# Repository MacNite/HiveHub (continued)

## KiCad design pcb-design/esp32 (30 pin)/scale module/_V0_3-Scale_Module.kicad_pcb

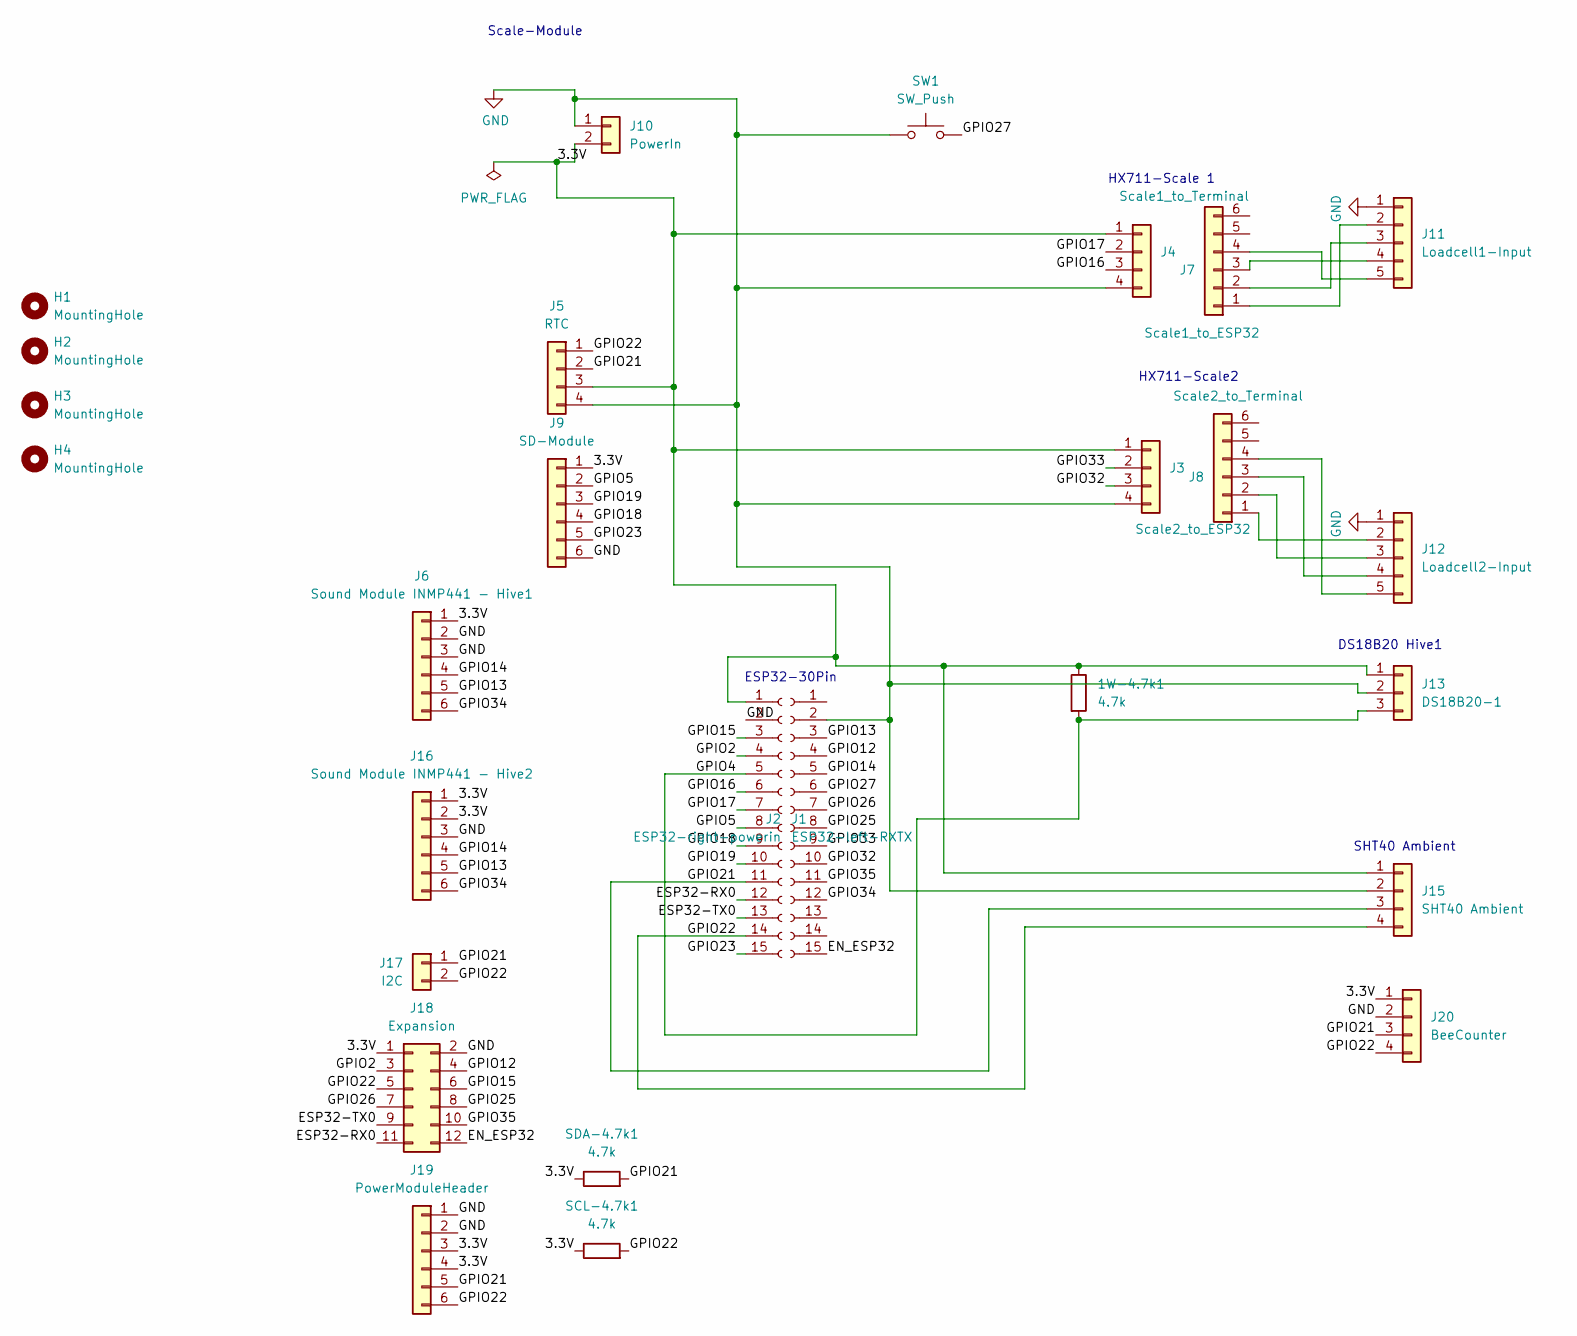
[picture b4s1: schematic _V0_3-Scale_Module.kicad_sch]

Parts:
1W-4.7k1: 4.7k; R_Axial_DIN0207_L6.3mm_D2.5mm_P7.62mm_Horizontal
H1, H2, H3, H4: MountingHole; MountingHole_3.2mm_M3
J1: ESP32-left-RXTX; PinSocket_1x15_P2.54mm_Vertical
J2: ESP32-right-powerin; PinHeader_1x15_P2.54mm_Vertical
J3: Scale2_to_ESP32; PinSocket_1x04_P2.54mm_Vertical
J4: Scale1_to_ESP32; PinSocket_1x04_P2.54mm_Vertical
J5: RTC; PinSocket_1x04_P2.54mm_Vertical
J6: Sound Module INMP441 - Hive1; JST_XH_B6B-XH-A_1x06_P2.50mm_Vertical
J7: Scale1_to_Terminal; PinSocket_1x06_P2.54mm_Vertical
J8: Scale2_to_Terminal; PinSocket_1x06_P2.54mm_Vertical
J9: SD-Module; PinSocket_1x06_P2.54mm_Vertical
J10: PowerIn; TerminalBlock_Xinya_XY308-2.54-2P_1x02_P2.54mm_Horizontal
J11: Loadcell1-Input; JST_XH_B5B-XH-A_1x05_P2.50mm_Vertical
J12: Loadcell2-Input; JST_XH_B5B-XH-A_1x05_P2.50mm_Vertical
J13: DS18B20-1; JST_XH_B3B-XH-A_1x03_P2.50mm_Vertical
J15: SHT40 Ambient; JST_XH_B4B-XH-A_1x04_P2.50mm_Vertical
J16: Sound Module INMP441 - Hive2; JST_XH_B6B-XH-A_1x06_P2.50mm_Vertical
J17: I2C; TerminalBlock_Xinya_XY308-2.54-2P_1x02_P2.54mm_Horizontal
J18: Expansion; PinHeader_2x06_P2.54mm_Vertical
J19: PowerModuleHeader; PinHeader_1x06_P2.54mm_Vertical
J20: BeeCounter; JST_XH_B4B-XH-A_1x04_P2.50mm_Vertical
SCL-4.7k1: 4.7k; R_Axial_DIN0207_L6.3mm_D2.5mm_P7.62mm_Horizontal
SDA-4.7k1: 4.7k; R_Axial_DIN0207_L6.3mm_D2.5mm_P7.62mm_Horizontal
SW1: SW_Push; PinSocket_1x02_P2.54mm_Vertical

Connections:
/3.3V: 1W-4.7k1.1, J1.1, J3.1, J4.1, J5.3, J6.1, J9.1, J10.2, J13.1, J15.1, J16.1, J16.2, J18.1, J19.3, J19.4, J20.1, SCL-4.7k1.1, SDA-4.7k1.1
/EN_ESP32: J2.15, J18.12
/ESP32-RX0: J1.12, J18.11
/ESP32-TX0: J1.13, J18.9
/GPIO2: J1.4, J18.3
/GPIO4: 1W-4.7k1.2, J1.5, J13.3
/GPIO5: J1.8, J9.2
/GPIO12: J2.4, J18.4
/GPIO13: J2.3, J6.5, J16.5
/GPIO14: J2.5, J6.4, J16.4
/GPIO15: J1.3, J18.6
/GPIO16: J1.6, J4.3
/GPIO17: J1.7, J4.2
/GPIO18: J1.9, J9.4
/GPIO19: J1.10, J9.3
/GPIO21: J1.11, J5.2, J15.3, J17.1, J19.5, J20.3, SDA-4.7k1.2
/GPIO22: J1.14, J5.1, J15.4, J17.2, J18.5, J19.6, J20.4, SCL-4.7k1.2
/GPIO23: J1.15, J9.5
/GPIO25: J2.8, J18.8
/GPIO26: J2.7, J18.7
/GPIO27: J2.6, SW1.2
/GPIO32: J2.10, J3.3
/GPIO33: J2.9, J3.2
/GPIO34: J2.12, J6.6, J16.6
/GPIO35: J2.11, J18.10
GND: J1.2, J2.2, J3.4, J4.4, J5.4, J6.2, J6.3, J9.6, J10.1, J11.1, J12.1, J13.2, J15.2, J16.3, J18.2, J19.1, J19.2, J20.2, SW1.1
unnamed: J7.1, J11.2
unnamed: J7.2, J11.3
unnamed: J7.3, J11.4
unnamed: J7.4, J11.5
unnamed: J8.1, J12.2
unnamed: J8.2, J12.3
unnamed: J8.3, J12.4
unnamed: J8.4, J12.5

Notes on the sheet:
Scale-Module
HX711-Scale2
DS18B20 Hive1
SHT40 Ambient
ESP32-30Pin
HX711-Scale 1

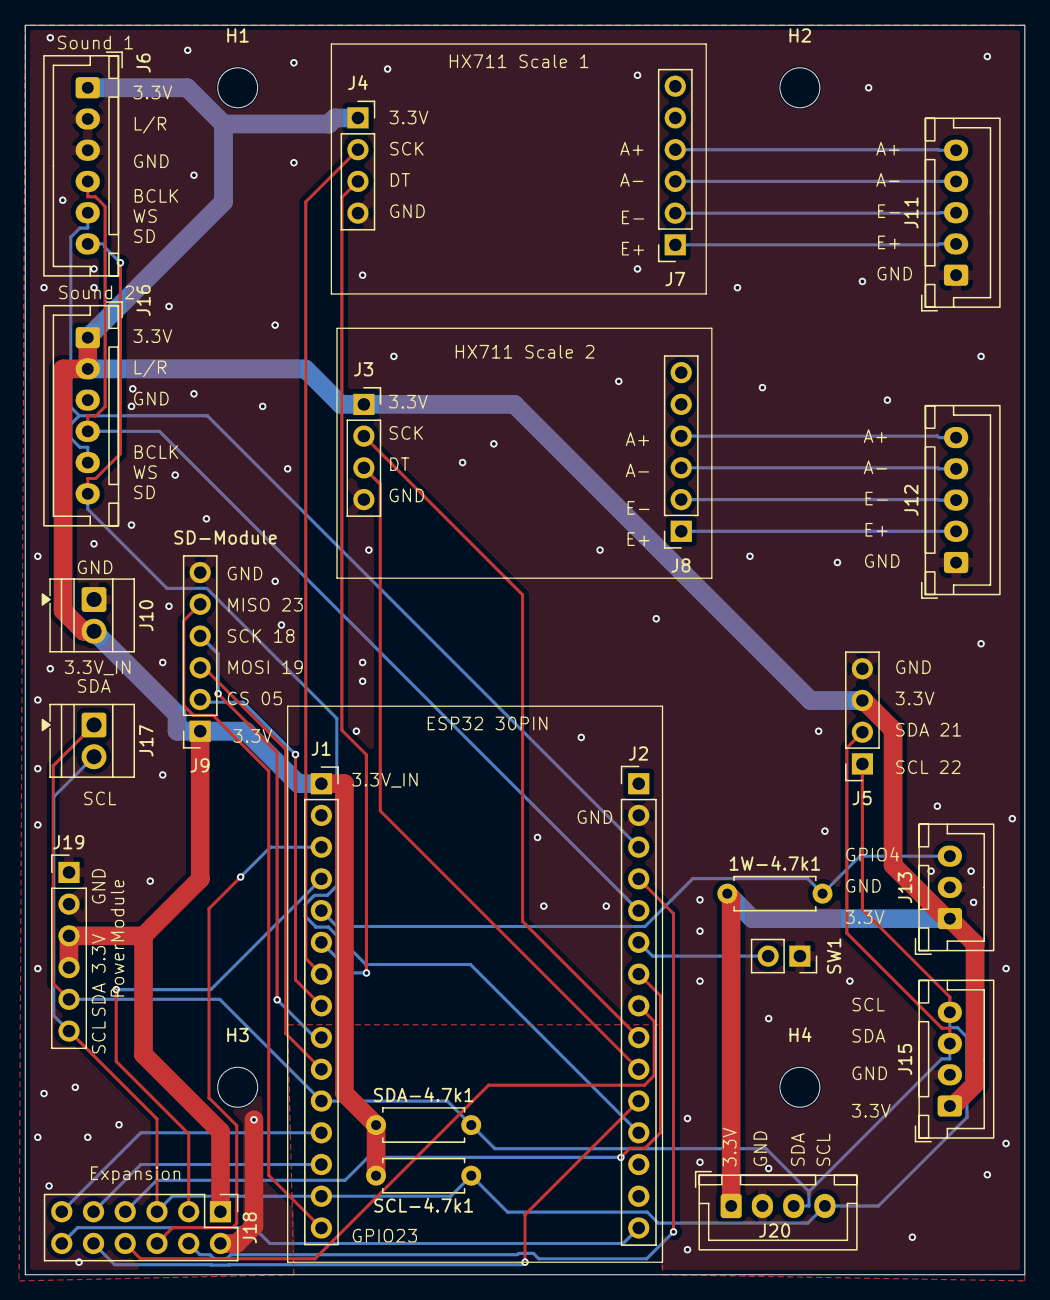
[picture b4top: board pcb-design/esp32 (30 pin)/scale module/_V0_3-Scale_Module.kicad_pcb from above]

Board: 2 copper layers, 80.0 x 100.0 mm, 27 parts (0 on the bottom side), 34 nets.

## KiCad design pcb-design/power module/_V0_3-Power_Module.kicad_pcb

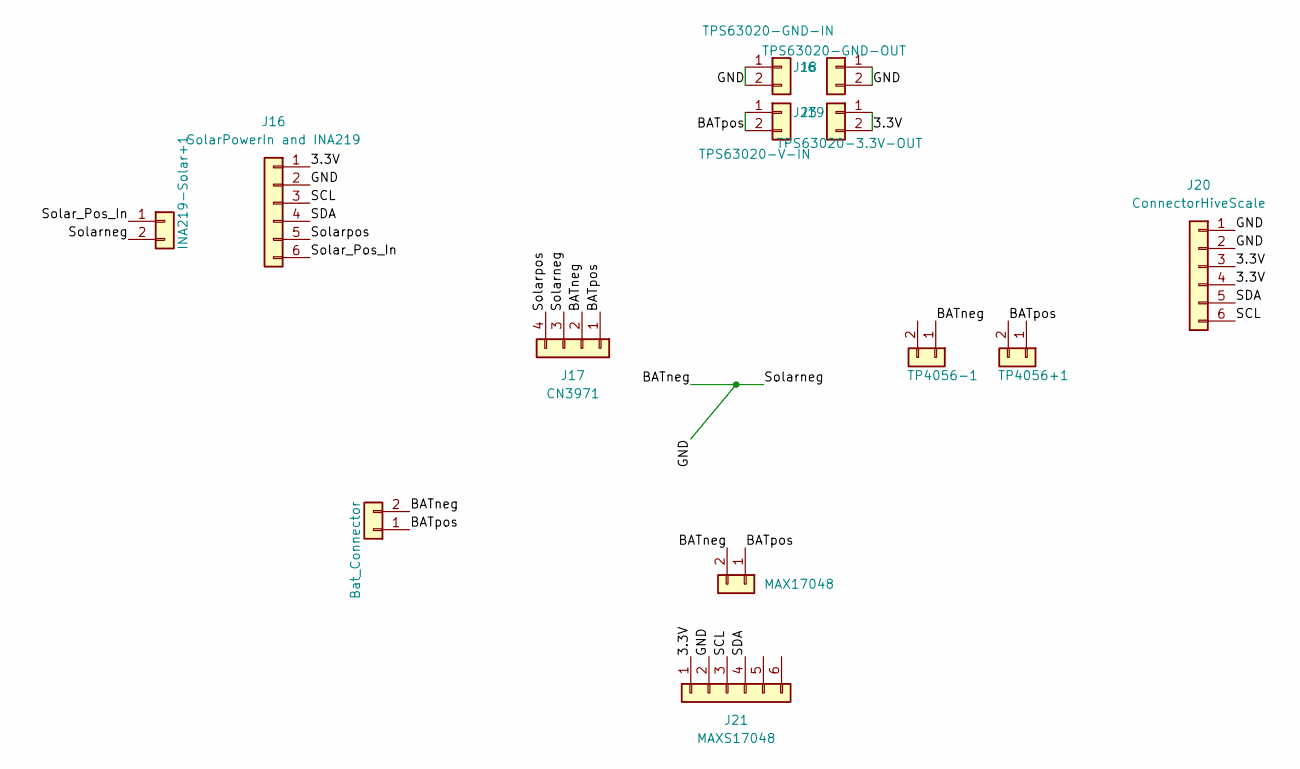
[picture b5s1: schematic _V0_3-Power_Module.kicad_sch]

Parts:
Bat_Connector: Battery; TerminalBlock_Xinya_XY308-2.54-2P_1x02_P2.54mm_Horizontal
INA219-Solar+1: Solar_Panel_In; TerminalBlock_Xinya_XY308-2.54-2P_1x02_P2.54mm_Horizontal
J6: TPS63020-GND-IN; PinSocket_1x02_P2.54mm_Vertical
J16: SolarPowerIn and INA219; PinSocket_1x06_P2.54mm_Vertical
J17: CN3971; PinSocket_1x04_P2.54mm_Vertical
J18: TPS63020-GND-OUT; PinSocket_1x02_P2.54mm_Vertical
J19: TPS63020-V-IN; PinSocket_1x02_P2.54mm_Vertical
J20: ConnectorHiveScale; PinHeader_1x06_P2.54mm_Vertical
J21: MAXS17048; PinSocket_1x06_P2.54mm_Vertical
J23: TPS63020-3.3V-OUT; PinSocket_1x02_P2.54mm_Vertical
MAX17048: BatteryMAX17048; PinSocket_1x02_P2.54mm_Vertical
TP4056+1, TP4056-1: BatteryMAX17048; PinSocket_1x02_P2.54mm_Vertical

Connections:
/3.3V: J16.1, J20.3, J20.4, J21.1, J23.1, J23.2
/BATneg: Bat_Connector.2, INA219-Solar+1.2, J6.1, J6.2, J16.2, J17.2, J17.3, J18.1, J18.2, J20.1, J20.2, J21.2, MAX17048.2, TP4056-1.1 (Pin_1_1); also elsewhere on the board
/BATpos: Bat_Connector.1, J17.1, J19.1, J19.2, MAX17048.1, TP4056+1.2 (Pin_2_2); also elsewhere on the board
/SCL: J16.3, J20.6, J21.3
/SDA: J16.4, J20.5, J21.4
/Solar_Pos_In: INA219-Solar+1.1, J16.6
/Solarpos: J16.5, J17.4

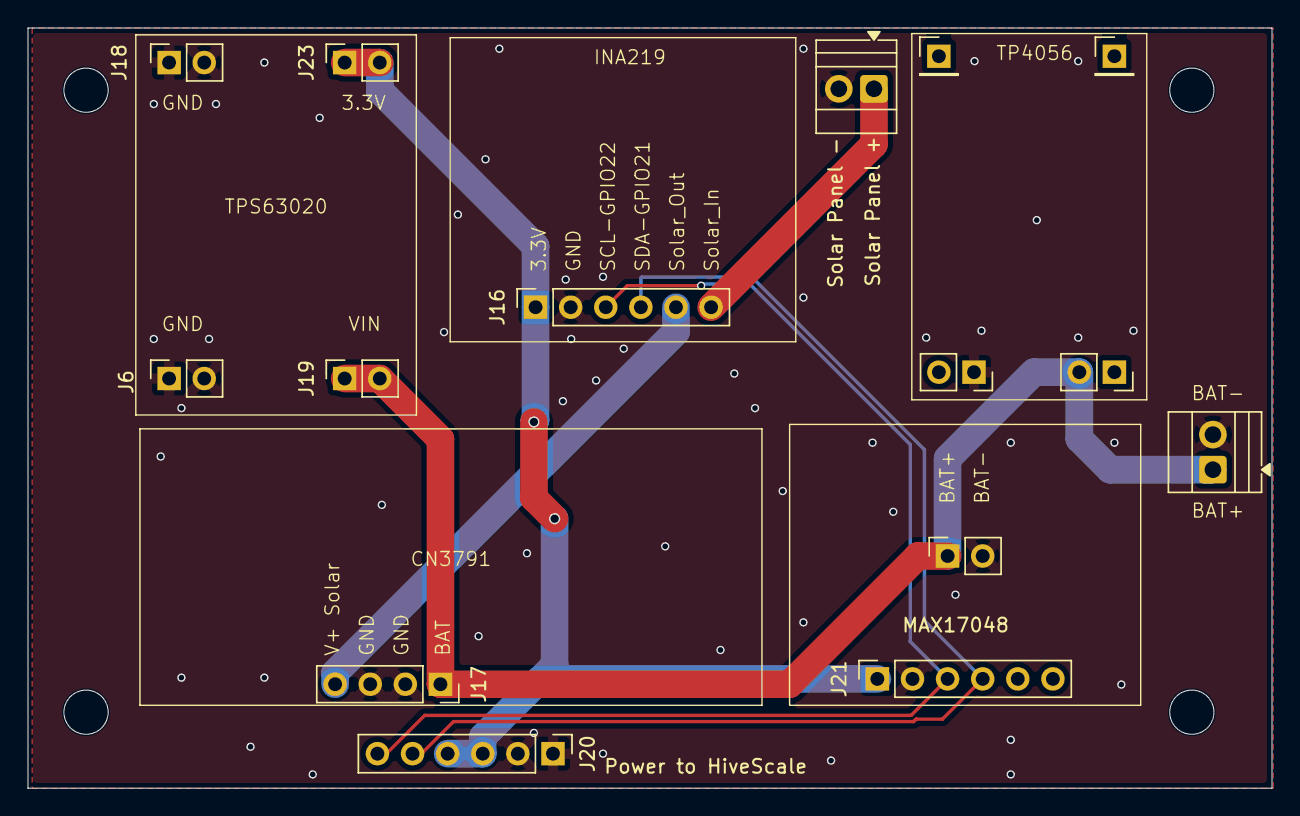
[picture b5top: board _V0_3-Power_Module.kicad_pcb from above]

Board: 2 copper layers, 90.0 x 55.0 mm, 19 parts (0 on the bottom side), 7 nets.

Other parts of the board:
Bat_Connector1: Battery; TerminalBlock_Xinya_XY308-2.54-2P_1x02_P2.54mm_Horizontal
m3-bl, m3-br, m3-tl, m3-tr: MountingHole_3.2mm_M3
stabilizer_usb_1, stabilizer_usb_2: PinHeader_1x01_P2.54mm_Vertical

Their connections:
/BATneg: Bat_Connector1.2; also elsewhere on the board
/BATpos: Bat_Connector1.1; also elsewhere on the board

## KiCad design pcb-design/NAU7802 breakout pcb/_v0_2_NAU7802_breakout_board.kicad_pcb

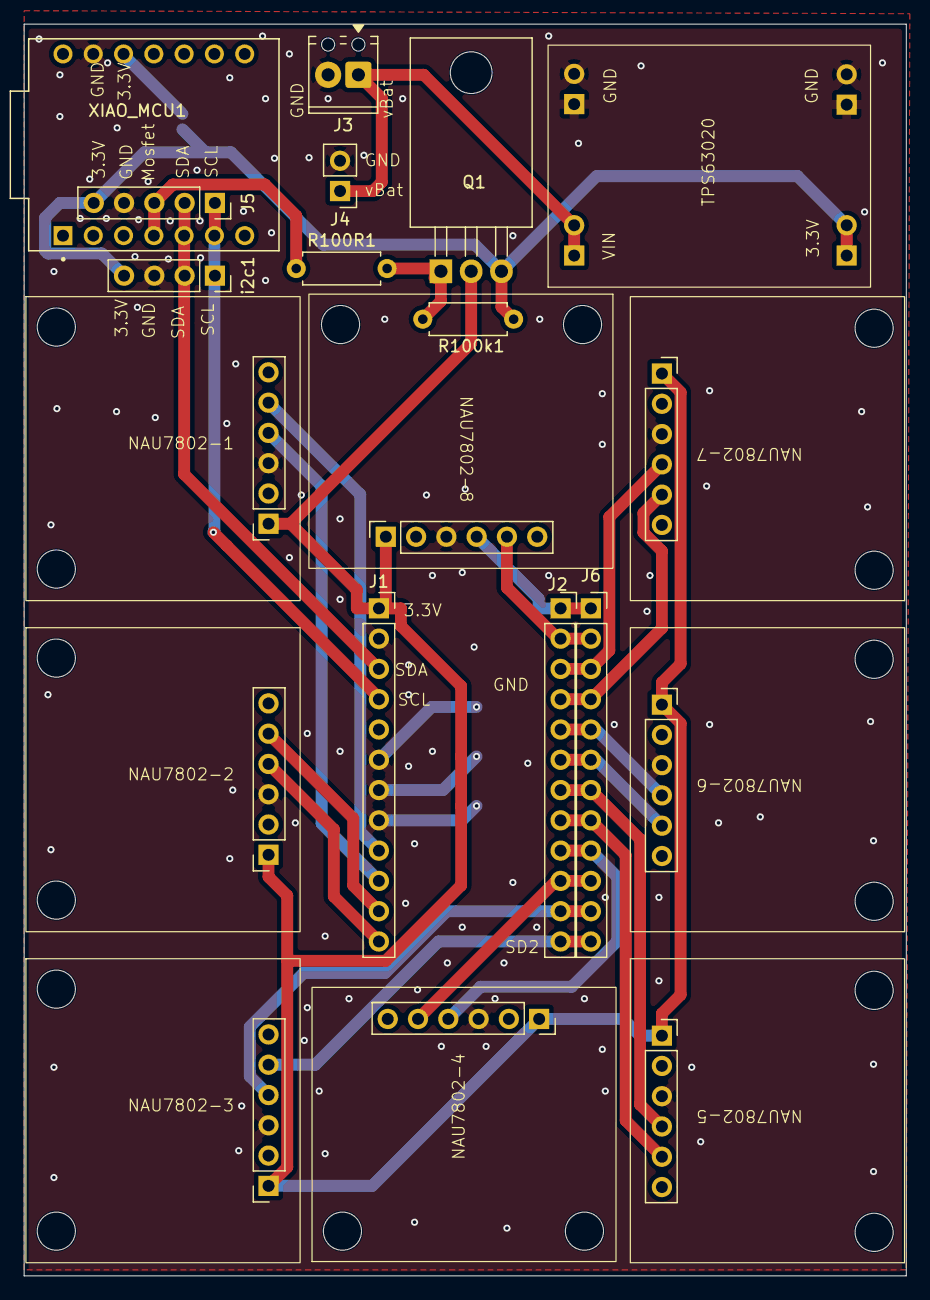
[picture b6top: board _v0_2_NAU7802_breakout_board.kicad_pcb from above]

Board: 2 copper layers, 74.0 x 105.0 mm, 21 parts (1 on the bottom side), 25 nets.

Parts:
J1: TCA9548A_L; PinSocket_1x12_P2.54mm_Vertical
J2, J6: TCA9548A_R; PinSocket_1x12_P2.54mm_Vertical
J3: Conn_01x02_Pin; TerminalBlock_Phoenix_MPT-0,5-2-2.54_1x02_P2.54mm_Horizontal
J4: Conn_01x02_Pin; PinHeader_1x02_P2.54mm_Vertical
J5: Conn_01x05_Pin; PinSocket_1x05_P2.54mm_Vertical
JP1: SolderJumper_2_Open; SolderJumper-2_P1.3mm_Open_RoundedPad1.0x1.5mm
NAU7802-1, NAU7802-2, NAU7802-3, NAU7802-4, NAU7802-5, NAU7802-6, NAU7802-7, NAU7802-8: NAU7802
Q1: Q_PMOS_GDS; TO-220-3_Horizontal_TabDown
R100R1, R100k1: R; R_Axial_DIN0207_L6.3mm_D2.5mm_P7.62mm_Horizontal
TPS63020: Conn_01x04_Pin; TPS6020
XIAO_MCU1: 113991254; MODULE_113991254
i2c1: Conn_01x04_Pin; PinSocket_1x04_P2.54mm_Vertical

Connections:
/3.3V: J5.5, JP1.2 (B), Q1.3 (S), R100k1.2, TPS63020.4, i2c1.4
/3.3V_powergated: J1.1, NAU7802-1.1, NAU7802-2.1, NAU7802-3.1, NAU7802-4.1, NAU7802-5.1, NAU7802-6.1, NAU7802-7.1, NAU7802-8.1, Q1.2 (D)
/D3: J5.3, R100R1.1, XIAO_MCU1.4 (D3)
/D4: J1.3, J5.2, XIAO_MCU1.5 (D4), i2c1.2
/D5: J1.4, J5.1, XIAO_MCU1.6 (D5), i2c1.1
/GND: J1.2, J1.6, J1.7, J1.8, J3.2, J4.2, J5.4, NAU7802-1.3, NAU7802-2.3, NAU7802-3.3, NAU7802-4.3, NAU7802-5.3, NAU7802-6.3, NAU7802-7.3, NAU7802-8.3, TPS63020.2, TPS63020.3, XIAO_MCU1.13 (GND), i2c1.3
/SC0: J1.10, NAU7802-1.4
/SC1: J1.12, NAU7802-2.4
/SC2: J2.11, J6.11, NAU7802-3.4
/SC3: J2.9, J6.9, NAU7802-4.4
/SC4: J2.7, J6.7, NAU7802-5.4
/SC5: J2.5, J6.5, NAU7802-6.4
/SC6: J2.3, J6.3, NAU7802-7.4
/SC7: J2.1, J6.1, NAU7802-8.4
/SD0: J1.9, NAU7802-1.5
/SD1: J1.11, NAU7802-2.5
/SD2: J2.12, J6.12, NAU7802-3.5
/SD3: J2.10, J6.10, NAU7802-4.5
/SD4: J2.8, J6.8, NAU7802-5.5
/SD5: J2.6, J6.6, NAU7802-6.5
/SD6: J2.4, J6.4, NAU7802-7.5
/SD7: J2.2, J6.2, NAU7802-8.5
/vBat: J3.1, J4.1, TPS63020.1
unnamed: JP1.1 (A), XIAO_MCU1.12 (3V3)
unnamed: Q1.1 (G), R100R1.2, R100k1.1

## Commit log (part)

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2026-05-14 Added fotos to known issues
2026-05-24 Removed LTE Modem, added sound monitoring
2026-05-26 Fixed compile error
2026-05-27 Fixed Stack Overflow error
2026-05-27 Added beecounter to firmware and backend
2026-05-28 firmware update
2026-05-28 FW Version
2026-05-30 Added OTA Updated for beecounter
2026-05-31 fixed requierements
2026-06-04 fixed fw version
2026-06-08 added sd-upload-documentation
2026-06-09 added temperatur compensation
2026-06-11 updated docs
2026-06-13 Updated pcb state
2026-06-15 added pcb fotos
2026-06-15 updated provisioning portal
2026-06-16 added connector for solar panel to power module
2026-06-16 re-upladed files
2026-06-16 added page
2026-06-16 added pages.yml
2026-06-16 added ble handling
2026-06-17 added GATT for BLE sensors
2026-06-17 updated versioning
2026-06-17 added support beehivemonitoring.com devices and updated config tool, added support for up to 6 wireless sensors.
2026-06-17 GATT updated
2026-06-17 updated GATT pairing
2026-06-17 bugfixing
2026-06-17 NimBLEDevice fix
2026-06-17 fixed connection termination on beehivemonitoring.com devices
2026-06-17 fixed hiveheart voltage decoding
2026-06-18 fixed beecounter ota crc
2026-06-19 updated pcb design
2026-06-19 updated beecounter ble connection
2026-06-19 added ble mode for beecounter
2026-06-19 updated fw number
2026-06-19 bumped fw-number
2026-06-21 Add HiveInside wake-sync write to GATT cycle; bump version to 0.16.10
    Each time HiveScale reads a HiveInside measurement over GATT it now also
    writes the next sleep duration to the writable CHR_SYNC characteristic
    (8e8b0003-…). HiveInside uses this value instead of its fixed
    MEASURE_INTERVAL_MS so it wakes just before HiveScale's next scan rather
    than staying connectable continuously. A 30-second lead is subtracted to
    absorb RC-oscillator drift and scan start-up time; HiveInside's 45-second
2026-06-21 fix: move sendIntervalMs extern to file scope to avoid blesensor namespace collision
2026-06-25 fixed ble-gatt for more then 2 beehivemonitoring devices
2026-06-25 fixed rssi+sound data
2026-06-25 added missing fields to server
2026-06-25 updated 1 hive per scale, allowed ble scale
2026-06-25 updated in-hive sensor mapping
2026-06-26 added esp32 c6 pcb files
2026-06-26 added NAU7802 breakout pcb v0.1
2026-06-26 updated onewire-library for esp32-c6
2026-06-30 added logo
2026-06-30 namechange workflow
